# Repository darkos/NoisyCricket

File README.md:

# Noisy Cricket
Small guitar amplifier

https://www.electrosmash.com/noisy-cricket-analysis

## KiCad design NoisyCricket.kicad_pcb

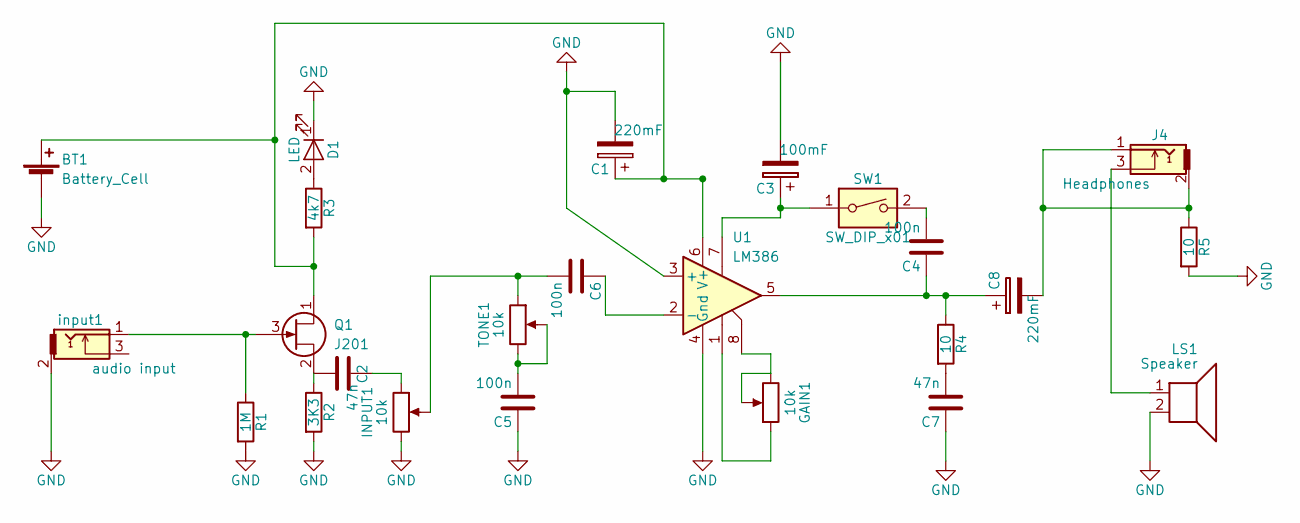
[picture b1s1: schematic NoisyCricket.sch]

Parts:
BT1: Battery_Cell; Pin_Header_Straight_1x02_Pitch2.54mm
C1, C8: 220mF; CP_Radial_D12.5mm_P2.50mm
C2, C7: 47n; C_Disc_D7.5mm_W5.0mm_P10.00mm
C3: 100mF; CP_Radial_D13.0mm_P7.50mm
C4, C5, C6: 100n; C_Disc_D7.5mm_W5.0mm_P10.00mm
D1: LED; LED_D3.0mm
GAIN1: 10k; Pin_Header_Straight_1x03_Pitch2.54mm
INPUT1: 10k; Pin_Header_Straight_1x03_Pitch2.54mm
J4: Headphones; Pin_Header_Straight_1x03_Pitch2.00mm
LS1: Speaker; Pin_Header_Straight_1x02_Pitch2.00mm
Q1: J201; OldSowjetaera_Transistor_Type-I_SmallPads
R1: 1M; R_Axial_DIN0411_L9.9mm_D3.6mm_P7.62mm_Vertical
R2: 3K3; R_Axial_DIN0411_L9.9mm_D3.6mm_P7.62mm_Vertical
R3: 4k7; R_Axial_DIN0411_L9.9mm_D3.6mm_P7.62mm_Vertical
R4, R5: 10; R_Axial_DIN0411_L9.9mm_D3.6mm_P7.62mm_Vertical
SW1: SW_DIP_x01; SW_DIP_x1_W7.62mm_Slide_LowProfile
TONE1: 10k; Pin_Header_Straight_1x03_Pitch2.54mm
U1: LM386; DIP-8_W7.62mm
input1: audio input; Pin_Header_Straight_1x03_Pitch2.00mm

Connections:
GND: BT1.2 (-), C1.2, C3.2, C5.1, C7.1, D1.1 (K), INPUT1.3, LS1.2, R1.2, R2.2, R5.2, U1.3 (+), U1.4 (Gnd), input1.2
unnamed: BT1.1 (+), C1.1, Q1.1 (D), R3.2, U1.6 (V+)
unnamed: C2.1, INPUT1.1
unnamed: C2.2, Q1.2 (S), R2.1
unnamed: C3.1, SW1.1, U1.7
unnamed: C4.1, C8.1, R4.1, U1.5
unnamed: C4.2, SW1.2
unnamed: C5.2, TONE1.2, TONE1.3
unnamed: C6.1, U1.2 (-)
unnamed: C6.2, INPUT1.2, TONE1.1
unnamed: C7.2, R4.2
unnamed: C8.2, J4.1, J4.2, R5.1
unnamed: D1.2 (A), R3.1
unnamed: GAIN1.1, U1.1
unnamed: GAIN1.2, GAIN1.3, U1.8
unnamed: J4.3, LS1.1
unnamed: Q1.3 (G), R1.1, input1.1

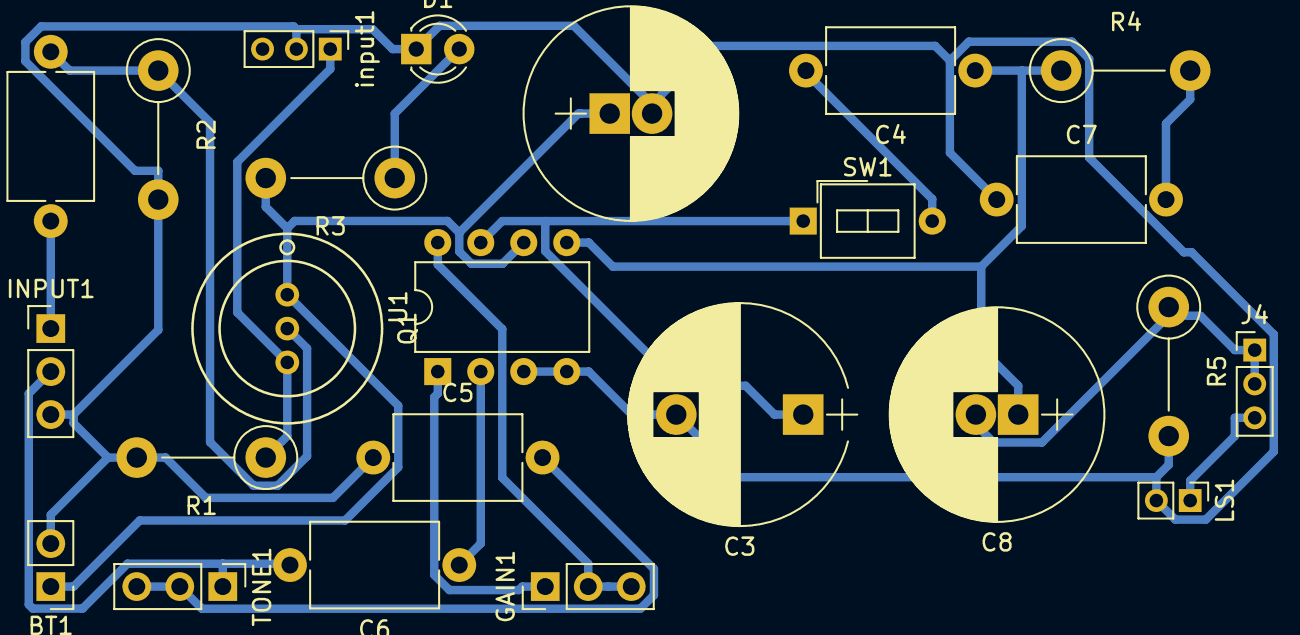
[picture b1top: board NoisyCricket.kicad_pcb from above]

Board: 2 copper layers, 24 parts (0 on the bottom side), 17 nets.

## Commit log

2018-11-20 adding readme
2018-11-20 complete with elements
2018-11-22 good for now
2018-11-22 one layer
2018-11-25 comonents little closer
